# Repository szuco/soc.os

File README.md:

# KiCad SwitchStack

Dreistufiges ESP32-Steuerungsmodul für eine massive Schalter-Unterputzdose (61 mm tief).
Drei gestapelte Leiterplatten steuern zwei 24-V-Jalousiemotoren, lesen Sensorik aus und
kommunizieren primär über RS-485. **Bottom und Mid sind rund (Ø 52 mm) und sitzen in der
Dose; Top ist quadratisch (47 × 47 mm) und sitzt davor** — hinter der Busch-Jaeger
Zentralscheibe 6435-914, deren Drucktasten in den Ecken liegen.

## Zentrale Designregel

Das System ist konsequent in drei Stör- und Leistungsdomänen getrennt:

| Ebene      | Projekt                        | Domäne                                   |
|------------|--------------------------------|------------------------------------------|
| **TOP**    | `hardware/top_ui`              | UI und Sensorik                          |
| **MID**    | `hardware/mid_logic`           | Digitale Logik und Kommunikation         |
| **BOTTOM** | `hardware/bottom_power_motor`  | 24-V-Leistung, Motoren, DC/DC            |

Hochstrom bleibt **vollständig** auf dem Bottom-Board. Die Board-to-Board-Stackverbinder
transportieren ausschließlich Signale und Kleinleistung. Diese Trennung ist für Bauraum,
EMV, Messqualität und Wartbarkeit zentral.

## Eckdaten

- Versorgung: 24 V DC über zwei Adern
- 2 × Klappladenmotor 24 V DC ±10 %, 2 Adern, Umpolung — Laufstrom ≈ 0,3–1,0 A, Blockierstrom offen
- Herrnhuter Mini-Weihnachtsstern 6,0–6,5 V / 0,5 W / ≈ 80 mA, nur im 24-V-Normalbetrieb
- USB-C ausschließlich für Programmierung und Debug
- Positionserkennung ausschließlich über Stromverlauf und Timeout, keine Endschalter
- KiCad-Version: **10.0.5** (migriert von 9.0.7, siehe `docs/08-kicad-workflow.md`)

## Dokumentation

| Dokument | Inhalt |
|---|---|
| [`docs/00-system-overview.md`](docs/00-system-overview.md) | Gesamtsystem, Peripherie, Board-Aufteilung |
| [`docs/01-power-tree.md`](docs/01-power-tree.md) | Power-Tree, Strombilanz, USB-ORing, Schutz |
| [`docs/02-motor-control.md`](docs/02-motor-control.md) | H-Bridges, Strommessung, Überstromschutz, Software-Konzept |
| [`docs/03-stack-pinout.md`](docs/03-stack-pinout.md) | Stackverbinder, verbindliches Pinmapping |
| [`docs/04-mechanical.md`](docs/04-mechanical.md) | Outline, Bohrbild, Koordinaten, Tiefenbudget |
| [`docs/05-manufacturing.md`](docs/05-manufacturing.md) | Lagenaufbau, Kupfer, DRC, Fertigungsdaten |
| [`docs/06-open-decisions.md`](docs/06-open-decisions.md) | Offene Bauteil- und Auslegungsentscheidungen |
| [`docs/07-roadmap.md`](docs/07-roadmap.md) | Konkrete Arbeitsschritte in Reihenfolge |
| [`docs/08-kicad-workflow.md`](docs/08-kicad-workflow.md) | KiCad-Konventionen, Bedienhinweise, Repo-Regeln |
| [`docs/09-display-and-mcu.md`](docs/09-display-and-mcu.md) | Displaywahl, MCU, GPIO-Budget, ESPHome-Grenzen |
| [`docs/10-firmware-strategy.md`](docs/10-firmware-strategy.md) | Firmware-Schichten, ESPHome-Unabhängigkeit, Modbus-Pfad |
| [`docs/11-motor-data.md`](docs/11-motor-data.md) | Motordatenblatt, Leistungsanalyse, **Messprotokoll M1–M7** |
| [`docs/12-legacy-socos.md`](docs/12-legacy-socos.md) | Vorgängerprojekt SoC OS: übernommene Anforderungen, verlorene Funktionen, Restriktionen |
| [`docs/13-funktionsstatus.md`](docs/13-funktionsstatus.md) | **Was steht, was fehlt** — Hardware, Firmware und Mechanik nebeneinander |
| [`hardware/bom/README.md`](hardware/bom/README.md) | Beschaffungsliste, Fertigerempfehlung, Bestellweg |

## Repository-Struktur

```
hardware/
  bottom_power_motor/   KiCad BOTTOM (24 V, Motor, DC/DC)
  mid_logic/            KiCad MID (ESP32-S3, RS-485, Expander, PhotoMOS, Piezo)
  top_ui/               KiCad TOP (USB-C, Display 1,69", 4 Ecktaster, SHT4x, ToF, Stern)
  lib/                  Gemeinsame Symbol-/Footprint-/3D-Bibliotheken
  bom/                  Beschaffung und Fertigerempfehlung
  fab/                  Erzeugte Fertigungsdaten und der Nutzen (Build-Ergebnis)
mechanical/             Adapter zur BJ-Zentralscheibe: build123d-Modell, STEP/STL
tools/                  Generatoren (Mechanik, Schaltpläne, Layouts, Routing, Fertigung)
firmware/
  esphome/              ESPHome-Konfiguration für Home Assistant
docs/                   Projektübergreifende Spezifikationen
```

Ein Verzeichnis `archive/` mit dem Altbestand der Vorgängerprojekte gab es bis zum
15.08.2026. Es ist ausgewertet und entfernt; das Ergebnis steht in
[`docs/12-legacy-socos.md`](docs/12-legacy-socos.md), die Dateien selbst liegen nur
noch in der Git-Historie.

## Erzeugen

Die mechanischen Teile sind **generiert, nicht handgezeichnet** — damit können die drei
Boards nicht auseinanderlaufen:

```bash
python3 tools/gen_boards.py          # 3 × .kicad_pcb: Outline, Bohrbild, Keepout
python3 tools/gen_bottom_sch.py      # Bottom-Schaltplan + BOM, mit Netzlistenprüfung
python3 tools/gen_mid_sch.py         # Mid-Schaltplan (ESP32, RS-485, Expander)
python3 tools/gen_top_sch.py         # Top-Schaltplan (USB-C, Taster, Sensorik)
python3 tools/gen_layouts.py         # 3 Layouts: Platzierung, Netze, Zonen, DRC
python3 tools/route_boards.py        # Freerouting-Pipeline (Container, s. docs/05)
python3 tools/gen_fab.py [board]     # Gerber/Drill/Pos + BOMs, nur nach DRC-Gate
python3 tools/gen_panel.py           # Fertigungsnutzen aus den drei Quellprojekten
python3 mechanical/adapter.py        # Adapter für die BJ-Zentralscheibe, mit Selbsttest
```

Jedes dieser Skripte prüft sein Ergebnis und meldet Abweichungen. `gen_boards.py`,
`gen_layouts.py`, `gen_fab.py` und `gen_panel.py` brauchen die `pcbnew`-Python-API aus
einer KiCad-Installation, `adapter.py` braucht `build123d` (`pip install build123d`),
`route_boards.py` einen Container (siehe `docs/05`).

Dazu zwei Werkzeuge ohne Hardware: `python3 tools/display_mock.py` zeichnet den
Displayinhalt als PNG, und `esphome compile firmware/esphome/switchstack.yaml`
übersetzt die Firmware vollständig.

Auch der Bottom-Schaltplan wird erzeugt: Die Konnektivität steht als Quelltext, und
nach dem Schreiben liest `kicad-cli` die Netzliste zurück und vergleicht sie gegen
genau diese Vorgabe. Das Ergebnis ist zweckmäßig gezeichnet, aber nachweislich
korrekt — und in KiCad frei umarrangierbar.

## Status

Vollständige Gegenüberstellung von umgesetzten und fehlenden Funktionen:
[`docs/13-funktionsstatus.md`](docs/13-funktionsstatus.md).

| Teil | Stand |
|---|---|
| Systemspezifikation, Power-Tree, Pinmapping | dokumentiert |
| Mechanik der drei Boards | erzeugt und verifiziert |
| Front | **Serienteil**: BJ-Zentralscheibe 6435-914 im Rahmen 1721-914. Der **Adapter** dazwischen ist erzeugt und selbstgeprüft (`mechanical/adapter.py`) |
| Schaltpläne aller drei Boards + Stücklisten | **erzeugt und netzlistengeprüft** — Schaltungsreview gegen Datenblätter steht aus |
| Layouts aller drei Boards: Platzierung + Zonen | **erzeugt, DRC ohne Platzierungsfehler** |
| **Routing BOTTOM** | 985 Segmente, 102 Vias, **43 Verbindungen offen** — Rest Handarbeit (docs/05 verlangt das für Leistungspfade ohnehin) |
| **Routing MID** | **746 Segmente, 104 Vias** (16.08.2026, Container). Offen: 18 Signalverbindungen und **ein Kurzschluss** `HOOD_B`/`RELAY_LED` an einer Stelle — Handarbeit, s. docs/05 |
| **Routing TOP** | **197 Segmente, 12 Vias** (16.08.2026, Container). Offen: 14 Signale, darunter **alle vier Tastenleitungen und drei USB-Netze**; dazu **eine neue Kollision** einer Leiterbahn mit dem Befestigungsloch der USB-Buchse |
| Fertigungsnutzen (3 Platinen in einer Boarddatei) | **erzeugt:** `hardware/fab/panel/` — 173,4 × 64,4 mm, zwei Kreise + ein Quadrat |
| Fertigungsdaten | **keine** — `python3 tools/gen_fab.py` nach dem Routing, mit DRC-Gate |
| ESPHome-Firmware | **übersetzt** (`esphome compile`, 2026.7.4 / IDF 5.5.5): RAM 35 %, Flash 56 %. Alle Lambdas geprüft. Motoren fahren **auf Zeit** |
| Lasterkennung, ToF-Distanz, RS-485-Protokoll | **fehlen** — die ersten beiden brauchen eine eigene C++-Komponente, s. docs/13 |
| Gefertigt oder gemessen | **nichts** |

Nächste Schritte: [`docs/07-roadmap.md`](docs/07-roadmap.md).
Der kritische Pfad ist die Messung des Blockierstroms — Messprotokoll in
[`docs/11-motor-data.md`](docs/11-motor-data.md), Abschnitt 4. Ohne sie bleiben
Sicherungen, Trip-Schwellen, Treiberauswahl und Steckverbinder provisorisch.

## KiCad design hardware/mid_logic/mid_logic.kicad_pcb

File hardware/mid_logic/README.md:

# MID – Logic

KiCad-Projekt `mid_logic`. Logik- und Kommunikationsebene des Stacks.

## Umfang

Bestückt sind 37 Bauteile, 57 Netze (`bom_mid.csv`):

- **ESP32-S3-WROOM-1-N16R8** als zentrale Steuerung, RESET- und BOOT-Taster
- **MAX3485** als **primäre** Kommunikation: `RS485_DIR` schaltet DE und /RE
  gemeinsam, Fail-Safe-Bias 2 × 560 R, Terminierung 120 R als **DNP** (nur am
  Busende bestücken), JST-XH 3-polig
- **PCF8574** (0x20) als GPIO-Expander für die langsamen Signale: `HW_TRIP1/2`,
  `TRIP_RST`, `STAR_EN`, `PRESENCE_INT`, `RELAY_CTL`, `REED1/2` — **P0–P7 sind
  damit restlos belegt** (relevant für Punkt 34)
- **Piezo passiv** mit Treiberstufe — ein aktiver Summer kann keine Melodien
- **PhotoMOS AQY282GS** als potentialfreier Meldekontakt zur Dunstabzugshaube,
  **ausschließlich SELV**, mit 33-V-Klemmdiode
- **Feldstecker JST-SH 6-polig** für zwei Verschlusskontakte und die Haube,
  je Reed 10k Pull-up, 1k Serie und 5V6-ESD-Diode
- Stackverbinder `J_STK_A` und `J_STK_B` nach unten und nach oben

Ein externer ADC ist **nicht** bestückt — die Strommessung hängt am internen ADC
des S3 (offener Punkt 18). Die frühere Radar-Schnittstelle ist entfallen; der
Präsenzsensor sitzt als VL53L1X auf dem Top-Board.

## Kernregeln

- **Antennen-Keepout:** ESP32-Antennenbereich kupfer- und bauteilfrei auf **allen** Lagen,
  Antenne möglichst zur Front orientiert. WLAN ist sekundär — in einer massiven
  Unterputzdose ist die Performance realistisch schwach, deshalb RS-485 als primäre
  Kommunikation.
- Keine Motorströme, keine USB-Datenleitungen auf diesem Board.
- Durchgehende GND-Referenzlage, 4 Lagen empfohlen.

## Mechanik

- Ø 52,0 mm, 1,0 mm Dicke
- Bohrbild und Stackverbinder-Positionen **deckungsgleich** mit BOTTOM und TOP
- Abstand nach unten und nach oben je **10 mm** — gleicher Verbinder, gleicher Abstand

Exakte Koordinaten: [`../../docs/04-mechanical.md`](../../docs/04-mechanical.md)

## Referenzdokumente

- [`docs/03-stack-pinout.md`](../../docs/03-stack-pinout.md) – Pinmapping beider Verbinder
- [`docs/00-system-overview.md`](../../docs/00-system-overview.md) – Peripherieübersicht
- [`docs/06-open-decisions.md`](../../docs/06-open-decisions.md) – ESP32-Modul, Transceiver, ADC, Feldstecker
- [`docs/13-funktionsstatus.md`](../../docs/13-funktionsstatus.md) – Gesamtstand

## Status

**Schaltplan erzeugt und netzlistengeprüft** (`tools/gen_mid_sch.py`, 37 Bauteile,
57 Netze, Netzlistenvergleich bestanden). Stückliste `bom_mid.csv` aus derselben
Quelle.

**Layout:** platziert, Zonen angelegt — **aber ohne eine einzige Leiterbahn.**
Es gab einmal einen vollständig gerouteten Stand (655 Segmente, 73 Vias); der
Umbau auf Reed-Kontakte und Haubenkontakt am 15.08.2026 hat das Layout neu
erzeugt und die Verdrahtung damit verworfen. Sie ist neu zu ziehen — Pipeline:
`tools/route_boards.py`, Massenacharbeit mit `tools/gnd_*.py`.

**Nicht geprüft:** Schaltungsreview gegen Datenblätter (MAX3485-Pinbelegung,
PhotoMOS-LED-Strom). Die Netzliste stimmt mit der Sollvorgabe überein — mehr sagt
sie nicht.

**Offen und layoutrelevant:** Punkt 29 (der Feldstecker sitzt 0,4 mm neben einem
Keepout) und Punkt 34 (Sabotagekontakte hätten hier keinen Expanderpin mehr).

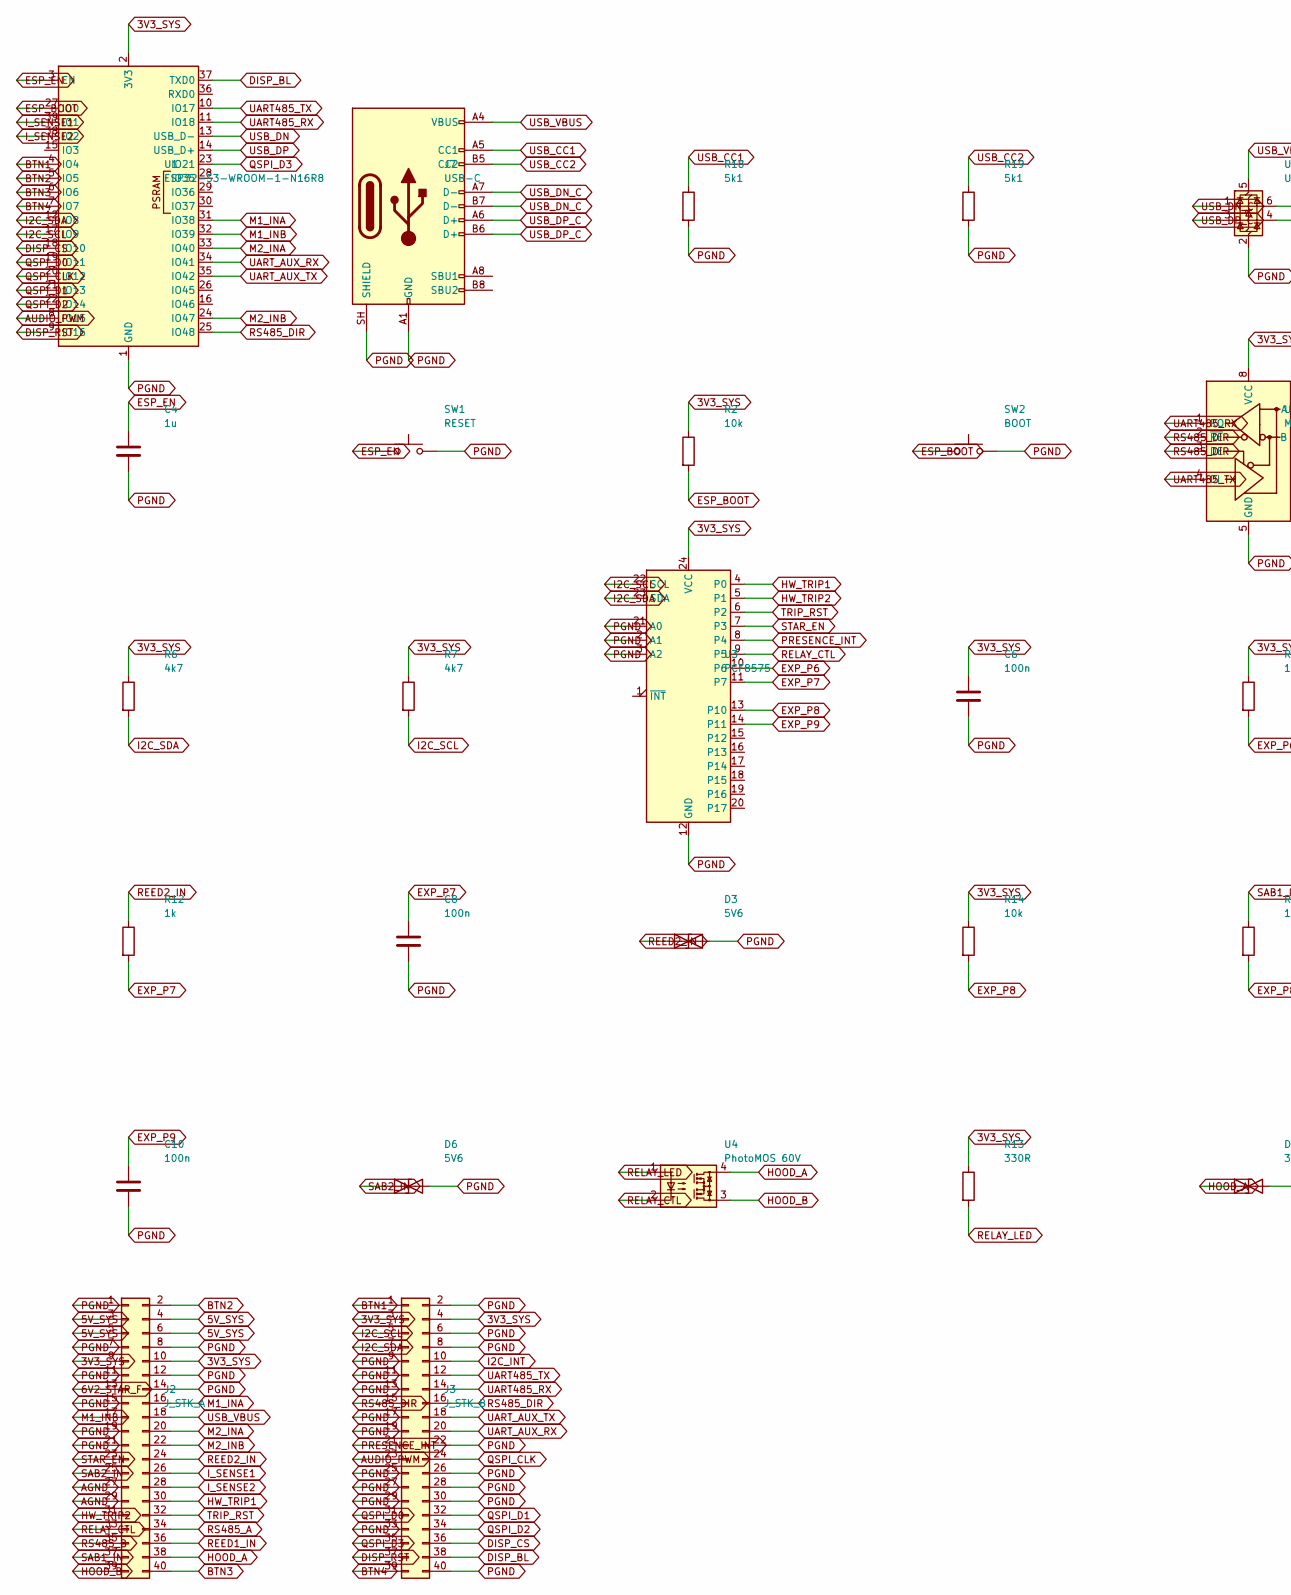
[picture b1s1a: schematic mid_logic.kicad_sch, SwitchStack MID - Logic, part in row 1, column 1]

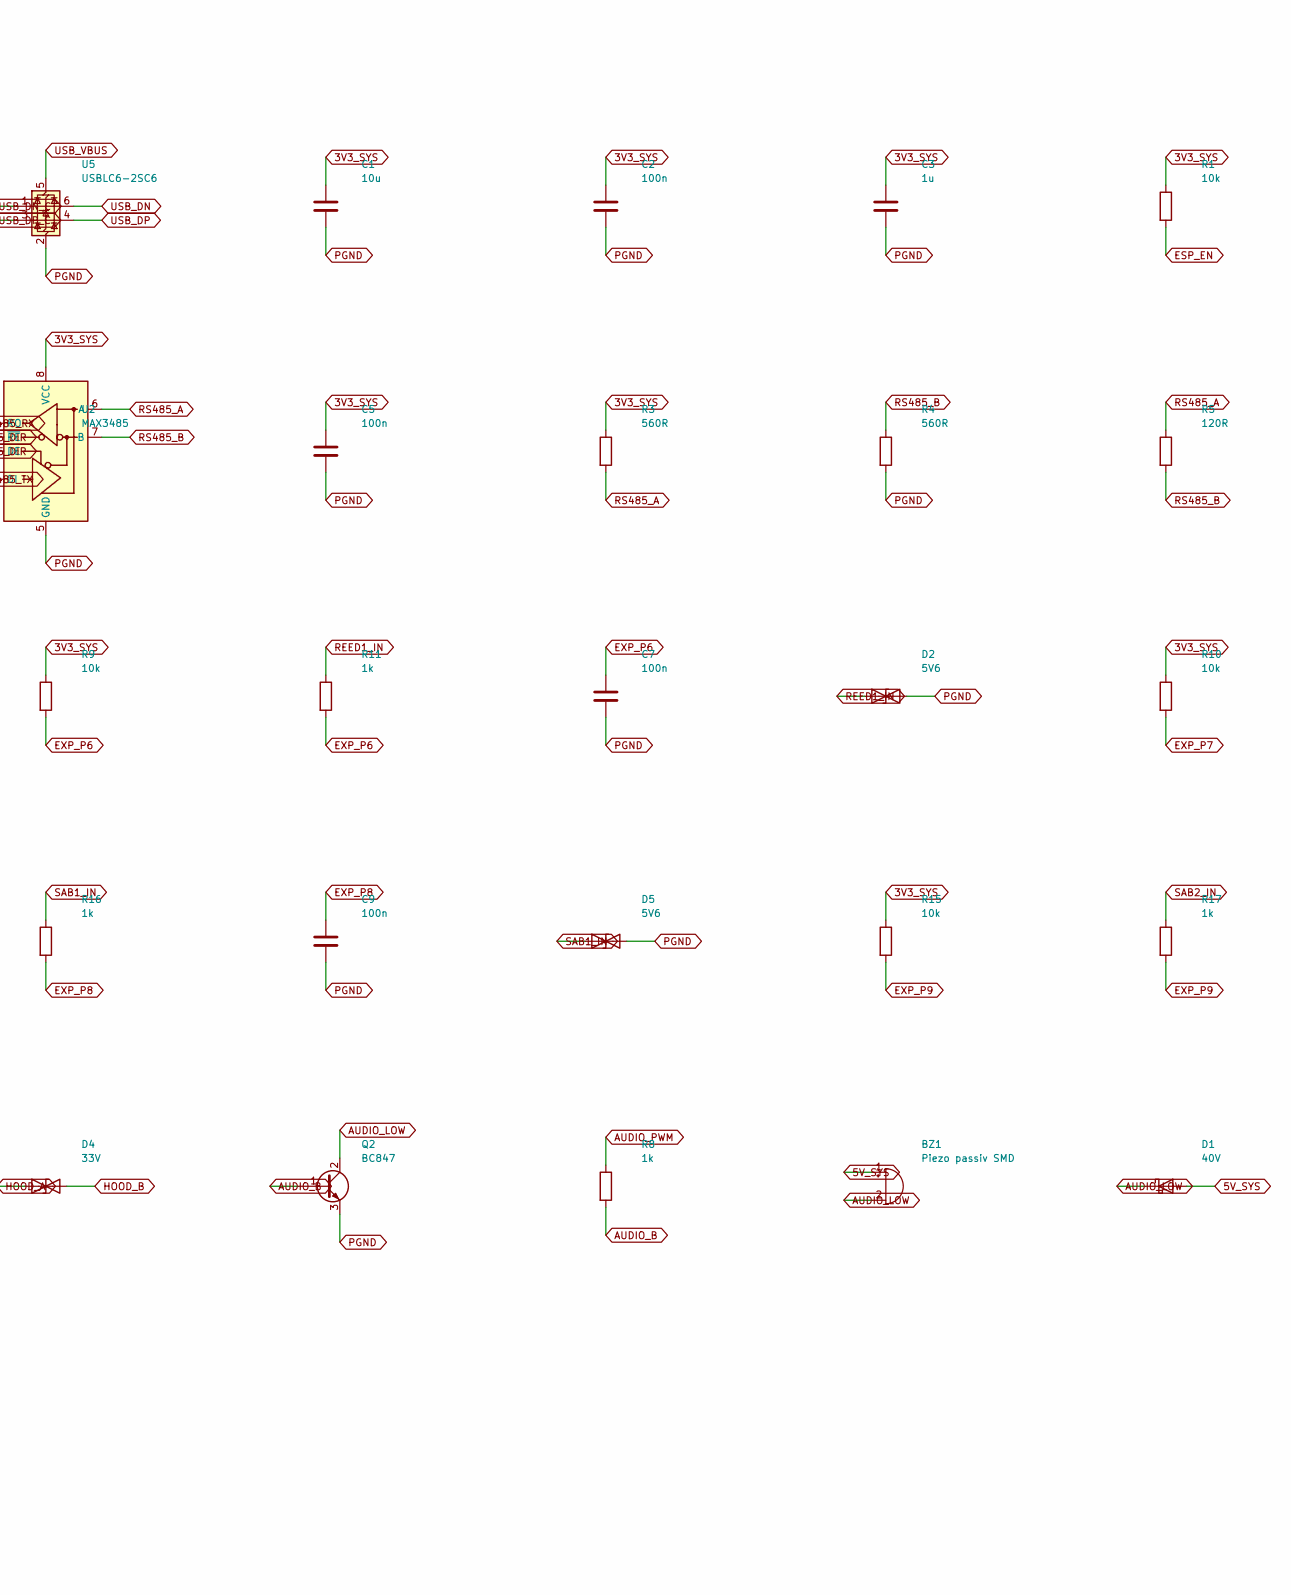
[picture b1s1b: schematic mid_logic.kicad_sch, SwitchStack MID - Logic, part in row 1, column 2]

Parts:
BZ1: Piezo passiv SMD; Buzzer_Murata_PKMCS0909E; MPN Murata PKMCS0909E o.ae., 9 x 9 x 3 mm S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
C1: 10u; C_0805_2012Metric
C2, C5, C6, C7, C8, C9, C10: 100n; C_0603_1608Metric
C3, C4: 1u; C_0603_1608Metric
D1: 40V; D_SOD-123
D2, D3, D5, D6: 5V6; D_SOD-123; MPN ESD am Feldstecker
D4: 33V; D_SOD-123; MPN Klemmung am Haubenausgang
J2: J_STK_A; PinHeader_2x20_P1.27mm_Vertical_Durchsteck
J3: J_STK_B; PinHeader_2x20_P1.27mm_Vertical_Durchsteck
J7: USB-C; USB_C_Receptacle_G-Switch_GT-USB-7051x; MPN G-Switch GT-USB-7051A/B, vertikal SMT (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
Q2: BC847; SOT-23
R1, R2: 10k; R_0603_1608Metric
R3: 560R; R_0603_1608Metric; MPN Fail-Safe-Bias A
R4: 560R; R_0603_1608Metric; MPN Fail-Safe-Bias B
R5: 120R; R_0603_1608Metric; MPN DNP - nur bestuecken, wenn dieses Gerae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
R6, R7: 4k7; R_0603_1608Metric
R8: 1k; R_0603_1608Metric
R9: 10k; R_0603_1608Metric; MPN Pullup Reed 1
R10: 10k; R_0603_1608Metric; MPN Pullup Reed 2
R11: 1k; R_0603_1608Metric; MPN Serie Reed 1
R12: 1k; R_0603_1608Metric; MPN Serie Reed 2
R13: 330R; R_0603_1608Metric; MPN LED-Strom PhotoMOS, ca. 6 mA
R14: 10k; R_0603_1608Metric; MPN Pullup Reed 3
R15: 10k; R_0603_1608Metric; MPN Pullup Reed 4
R16: 1k; R_0603_1608Metric; MPN Serie Reed 3
R17: 1k; R_0603_1608Metric; MPN Serie Reed 4
R18, R19: 5k1; R_0603_1608Metric
SW1: RESET; SW_SPST_TL3342
SW2: BOOT; SW_SPST_TL3342
U1: ESP32-S3-WROOM-1-N16R8; ESP32-S3-WROOM-1; MPN Antenne zeigt zur Front (+Y), Keepout a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
U2: MAX3485; SOIC-8_3.9x4.9mm_P1.27mm; MPN 3,3-V-Typ; Pinbelegung gegen Datenblatt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
U3: PCF8575; SSOP-24_5.3x8.2mm_P0.65mm; MPN Adresse 0x20: A0=A1=A2=GND - muss zur Y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
U4: PhotoMOS 60V; SOP-4_4.4x2.6mm_P1.27mm; MPN 1 Form A, SELV - NICHT fuer Netzspannung
U5: USBLC6-2SC6; SOT-23-6

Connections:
3V3_SYS: C1.1, C2.1, C3.1, C5.1, C6.1, J2.9, J2.10, J3.3, J3.4, R1.1, R2.1, R3.1, R6.1, R7.1, R9.1, R10.1, R13.1, R14.1, R15.1, U1.2 (3V3), U2.8 (VCC), U3.24 (VCC)
5V_SYS: BZ1.1 (+), D1.2 (A), J2.3, J2.4, J2.5, J2.6
6V2_STAR_F: J2.13
AGND: J2.27, J2.29
AUDIO_B: Q2.1 (B), R8.2
AUDIO_LOW: BZ1.2 (-), D1.1 (K), Q2.2 (C)
AUDIO_PWM: J3.23, R8.1, U1.8 (IO15)
BTN1: J3.1, U1.4 (IO4)
BTN2: J2.2, U1.5 (IO5)
BTN3: J2.40, U1.6 (IO6)
BTN4: J3.39, U1.7 (IO7)
DISP_BL: J3.38, U1.37 (TXD0)
DISP_CS: J3.36, U1.18 (IO10)
DISP_RST: J3.37, U1.9 (IO16)
ESP_BOOT: R2.2, SW2.1, U1.27 (IO0)
ESP_EN: C4.1, R1.2, SW1.1, U1.3 (EN)
EXP_P6: C7.1, R9.2, R11.2, U3.10 (P6)
EXP_P7: C8.1, R10.2, R12.2, U3.11 (P7)
EXP_P8: C9.1, R14.2, R16.2, U3.13 (P10)
EXP_P9: C10.1, R15.2, R17.2, U3.14 (P11)
HOOD_A: D4.1 (A1), J2.38, U4.4
HOOD_B: D4.2 (A2), J2.39, U4.3
HW_TRIP1: J2.30, U3.4 (P0)
HW_TRIP2: J2.31, U3.5 (P1)
I2C_INT: J3.10
I2C_SCL: J3.5, R7.2, U1.17 (IO9), U3.22 (SCL)
I2C_SDA: J3.7, R6.2, U1.12 (IO8), U3.23 (SDA)
I_SENSE1: J2.26, U1.39 (IO1)
I_SENSE2: J2.28, U1.38 (IO2)
M1_INA: J2.16, U1.31 (IO38)
M1_INB: J2.17, U1.32 (IO39)
M2_INA: J2.20, U1.33 (IO40)
M2_INB: J2.22, U1.24 (IO47)
PRESENCE_INT: J3.21, U3.8 (P4)
QSPI_CLK: J3.24, U1.20 (IO12)
QSPI_D0: J3.31, U1.19 (IO11)
QSPI_D1: J3.32, U1.21 (IO13)
QSPI_D2: J3.34, U1.22 (IO14)
QSPI_D3: J3.35, U1.23 (IO21)
REED1_IN: D2.1 (A1), J2.36, R11.1
REED2_IN: D3.1 (A1), J2.24, R12.1
RELAY_CTL: J2.33, U3.9 (P5), U4.2
RELAY_LED: R13.2, U4.1
RS485_A: J2.34, R3.2, R5.1, U2.6 (A)
RS485_B: J2.35, R4.1, R5.2, U2.7 (B)
RS485_DIR: J3.15, J3.16, U1.25 (IO48), U2.2 (~RE), U2.3 (DE)
SAB1_IN: D5.1 (A1), J2.37, R16.1
SAB2_IN: D6.1 (A1), J2.25, R17.1
STAR_EN: J2.23, U3.7 (P3)
TRIP_RST: J2.32, U3.6 (P2)
UART485_RX: J3.14, U1.11 (IO18), U2.1 (RO)
UART485_TX: J3.12, U1.10 (IO17), U2.4 (DI)
UART_AUX_RX: J3.20, U1.34 (IO41)
UART_AUX_TX: J3.18, U1.35 (IO42)
USB_CC1: J7.A5 (CC1), R18.1
USB_CC2: J7.B5 (CC2), R19.1
USB_DN: U1.13 (USB_D-), U5.6 (I/O1)
USB_DN_C: J7.A7 (D-), J7.B7 (D-), U5.1 (I/O1)
USB_DP: U1.14 (USB_D+), U5.4 (I/O2)
USB_DP_C: J7.A6 (D+), J7.B6 (D+), U5.3 (I/O2)
USB_VBUS: J2.18, J7.A4 (VBUS), J7.A9 (VBUS), J7.B4 (VBUS), J7.B9 (VBUS), U5.5 (VBUS)

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
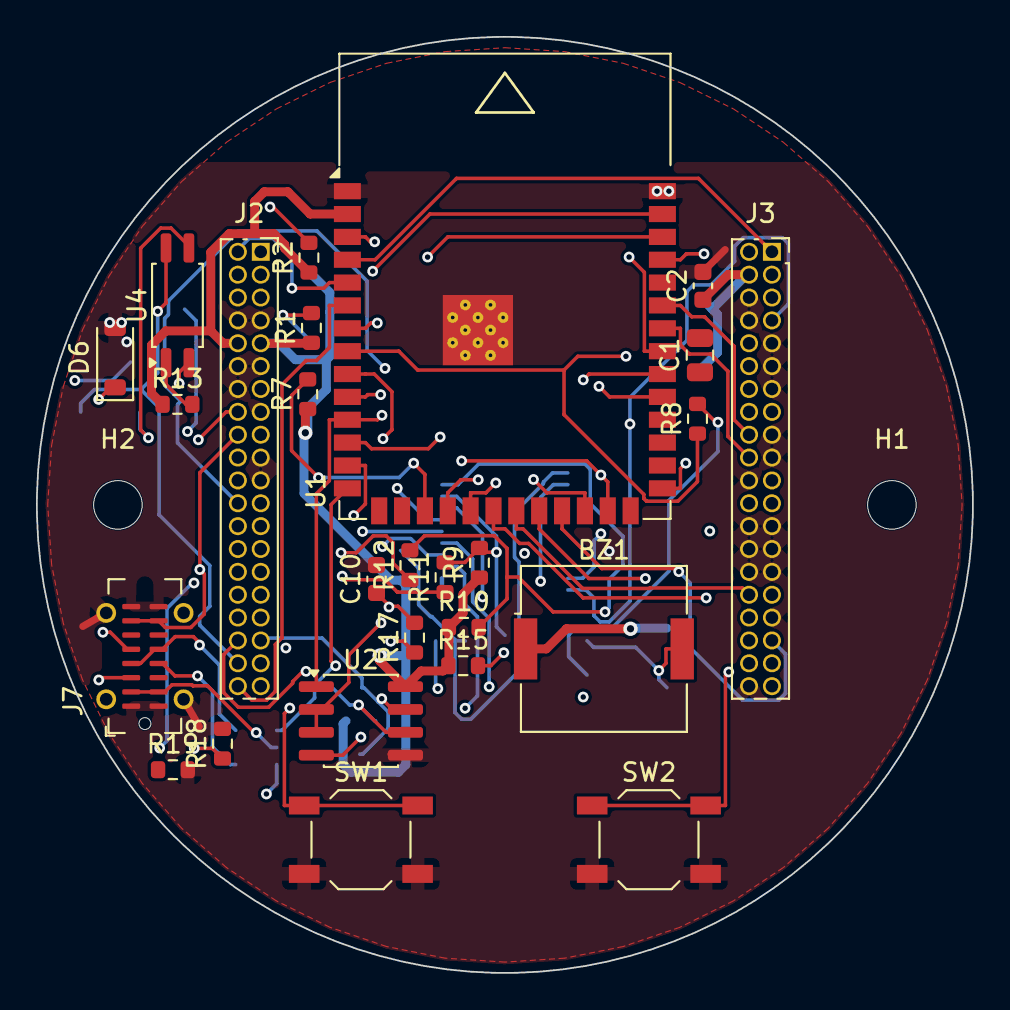
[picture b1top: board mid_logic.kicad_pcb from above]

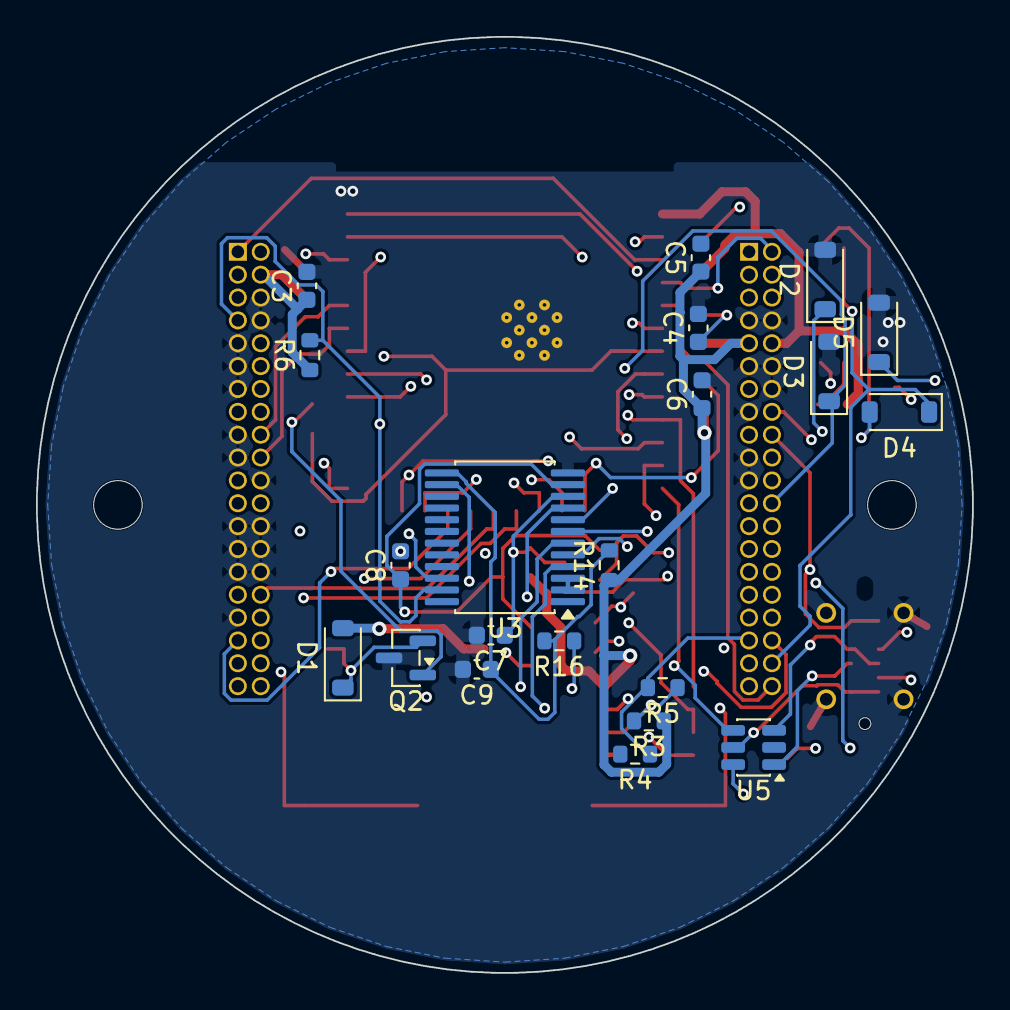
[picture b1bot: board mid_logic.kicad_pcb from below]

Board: 4 copper layers, 52.0 x 52.0 mm, 49 parts (21 on the bottom side), 60 nets.

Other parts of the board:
H1, H2: MountingHole_2.7mm_M2.5

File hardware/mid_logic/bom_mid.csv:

Menge,Designator,Wert,Footprint,Hinweis
1,BZ1,Piezo passiv SMD,Buzzer_Beeper:Buzzer_Murata_PKMCS0909E,"Murata PKMCS0909E o.ae., 9 x 9 x 3 mm SMD - passiv, ein aktiver Summer kann keine rtttl-Melodien. SMD statt des frueheren THT-Typs (12 x 9,5): der blockierte beide Platinenseiten, und auf der Rueckseite fehlte danach der Platz fuer den 16-Bit-Expander"
1,C1,10u,Capacitor_SMD:C_0805_2012Metric,
7,"C2,C5,C6,C7,C8,C9,C10",100n,Capacitor_SMD:C_0603_1608Metric,
2,"C3,C4",1u,Capacitor_SMD:C_0603_1608Metric,
1,D1,40V,Diode_SMD:D_SOD-123,
4,"D2,D3,D5,D6",5V6,Diode_SMD:D_SOD-123,ESD am Feldstecker
1,D4,33V,Diode_SMD:D_SOD-123,Klemmung am Haubenausgang
1,J2,J_STK_A,Connector_PinSocket_1.27mm:PinSocket_2x20_P1.27mm_Vertical,
1,J3,J_STK_B,Connector_PinSocket_1.27mm:PinSocket_2x20_P1.27mm_Vertical,
1,J4,RS485 A/B/GND,Connector_JST:JST_XH_B3B-XH-A_1x03_P2.50mm_Vertical,Kabel VOR dem Stapeln stecken - Zugaenglichkeit im Review pruefen
1,J5,Feld: 4 Reed,Connector_JST:JST_SH_BM06B-SRSS-TB_1x06-1MP_P1.00mm_Vertical,1 REED1 2 SAB1 3 GND | 4 REED2 5 SAB2 6 GND
1,J6,Haubenkontakt,Connector_JST:JST_SH_BM02B-SRSS-TB_1x02-1MP_P1.00mm_Vertical,potentialfrei ueber den PhotoMOS - NUR SELV
1,Q2,BC847,Package_TO_SOT_SMD:SOT-23,
2,"R1,R2",10k,Resistor_SMD:R_0603_1608Metric,
1,R3,560R,Resistor_SMD:R_0603_1608Metric,Fail-Safe-Bias A
1,R4,560R,Resistor_SMD:R_0603_1608Metric,Fail-Safe-Bias B
1,R5,120R,Resistor_SMD:R_0603_1608Metric,"DNP - nur bestuecken, wenn dieses Geraet am Busende sitzt"
2,"R6,R7",4k7,Resistor_SMD:R_0603_1608Metric,
1,R8,1k,Resistor_SMD:R_0603_1608Metric,
1,R9,10k,Resistor_SMD:R_0603_1608Metric,Pullup Reed 1
1,R10,10k,Resistor_SMD:R_0603_1608Metric,Pullup Reed 2
1,R11,1k,Resistor_SMD:R_0603_1608Metric,Serie Reed 1
1,R12,1k,Resistor_SMD:R_0603_1608Metric,Serie Reed 2
1,R13,330R,Resistor_SMD:R_0603_1608Metric,"LED-Strom PhotoMOS, ca. 6 mA"
1,R14,10k,Resistor_SMD:R_0603_1608Metric,Pullup Reed 3
1,R15,10k,Resistor_SMD:R_0603_1608Metric,Pullup Reed 4
1,R16,1k,Resistor_SMD:R_0603_1608Metric,Serie Reed 3
1,R17,1k,Resistor_SMD:R_0603_1608Metric,Serie Reed 4
1,SW1,RESET,Button_Switch_SMD:SW_SPST_TL3342,
1,SW2,BOOT,Button_Switch_SMD:SW_SPST_TL3342,
1,U1,ESP32-S3-WROOM-1-N16R8,RF_Module:ESP32-S3-WROOM-1,"Antenne zeigt zur Front (+Y), Keepout auf allen Lagen"
1,U2,MAX3485,Package_SO:SOIC-8_3.9x4.9mm_P1.27mm,"3,3-V-Typ; Pinbelegung gegen Datenblatt pruefen"
1,U3,PCF8575,Package_SO:SSOP-24_5.3x8.2mm_P0.65mm,Adresse 0x20: A0=A1=A2=GND - muss zur YAML passen
1,U4,PhotoMOS 60V,Package_SO:SOP-4_4.4x2.6mm_P1.27mm,"1 Form A, SELV - NICHT fuer Netzspannung"

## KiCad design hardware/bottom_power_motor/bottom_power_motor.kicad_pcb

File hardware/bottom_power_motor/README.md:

# BOTTOM – Power & Motor

KiCad-Projekt `bottom_power_motor`. Leistungsebene des Stacks.

## Umfang

- 24-V-Eingangsschutz: Sicherung, TVS, optionaler Verpolschutz
- Hochstrom-Steckverbinder nach unten, 6-polig
- Zwei Motor-H-Bridges für die Jalousiemotoren
- Strommessung getrennt pro Motor
- Hardwareseitige Überstromabschaltung, Comparator + Latch **pro Motor**
- DC/DC-Wandler: 24 → 5 V, 5 → 3,3 V, 24 → 6,2 V
- Mini-Relais (Zuordnung noch zu bestätigen)
- Stackverbinder `J_STK_A` und `J_STK_B` nach oben

## Kernregel

**Hochstrom bleibt vollständig auf diesem Board.** Motorströme werden niemals über die
Stackverbinder geführt.

## Mechanik

- Ø 52,0 mm, 1,0 mm Dicke
- Zwei Befestigungsbohrungen auf R = 21,5 mm bei 0° / 180° (Bohrbild v2, siehe docs/04)
- Bottom-Connector im Bereich −Y (unten), siehe Frontorientierung
- 2-oz-Kupfer prüfen

Exakte Koordinaten: [`../../docs/04-mechanical.md`](../../docs/04-mechanical.md)

## Referenzdokumente

- [`docs/01-power-tree.md`](../../docs/01-power-tree.md) – Power-Tree, Strombilanz, Schutz
- [`docs/02-motor-control.md`](../../docs/02-motor-control.md) – H-Bridges, Sense, Trip
- [`docs/03-stack-pinout.md`](../../docs/03-stack-pinout.md) – Stackverbinder
- [`docs/04-mechanical.md`](../../docs/04-mechanical.md) – Outline, Bohrbild, Tiefenbudget

## Dateien

| Datei | Stand |
|---|---|
| `bottom_power_motor.kicad_pcb` | Mechanik: Outline Ø 52 mm, Bohrbild, Dicke 1,0 mm |
| `bottom_power_motor.kicad_sch` | **Schaltplan, 103 Bauteile, 105 Netze** |
| `bom_bottom.csv` | Stückliste, aus derselben Quelle erzeugt |

Beides wird generiert, nicht von Hand gezeichnet:

```bash
python3 tools/gen_boards.py       # Mechanik
python3 tools/gen_bottom_sch.py   # Schaltplan + Stückliste + Netzlistenprüfung
```

## Status

**Schaltplan steht und ist netzlistengeprüft.** `tools/gen_bottom_sch.py` exportiert
nach dem Erzeugen die Netzliste mit `kicad-cli` und vergleicht sie gegen die im
Quelltext hinterlegte Soll-Konnektivität — 105 Netze, keine Abweichung, kein offener
Pin.

Enthalten: 24-V-Eingangsschutz (Sicherung, TVS, P-FET-Verpolschutz), 12-V-Gate-
Versorgung, drei DC/DC-Wandler, USB-ORing, Stern-Ausgang mit Polyfuse, zwei
vollständige H-Brücken aus je 2× IR2104 und 4 N-FETs, Inline-Strommessung mit
INA240A2, Fensterkomparator und Latch je Kanal, beide Stackverbinder.

**Was der Schaltplan noch nicht ist:**

- **Nicht geprüft im Sinne einer Schaltungsreview.** Werte sind gerechnet, aber die
  Regler sind noch nicht gegen die Hersteller-Referenzlayouts abgeglichen.
- **Pinbelegungen der ICs gegen die Datenblätter prüfen** — insbesondere INA240A2D,
  dessen KiCad-Symbol zwei GND-Pins gestapelt führt.
- **Die Darstellung ist zweckmäßig, nicht schön.** Jedes Bauteil hängt über kurze
  Stummel an globalen Labels. Das ist netzlistenidentisch mit einem gezeichneten Plan
  und lässt sich in KiCad frei umarrangieren, ohne die Verbindungen zu verlieren.

**Layout:** Platzierung generiert, Zonen gefüllt, **985 Segmente und 102 Vias**
geroutet, keine Kupferfehler. Offen sind **43 Verbindungen im Motor- und
Leistungsteil** (SW-Knoten, Gate-Netze, `24V_PROT`). Der Autorouter konvergiert
dort nicht mehr — und soll es auch nicht: Diese Pfade sind laut
[`docs/05`](../../docs/05-manufacturing.md) Abschnitt 3 **von Hand** zu ziehen,
kurz und breit, Buck-Schleifen nach Hersteller-Referenzlayout, Sternpunkt
AGND/PGND über R12. Erst danach greift das DRC-Gate von `gen_fab.py`.

Offene Bauteilposition: der N-Kanal-MOSFET (Punkt 8 in
[`docs/06`](../../docs/06-open-decisions.md)) — er hängt am noch nicht gemessenen
Blockierstrom.

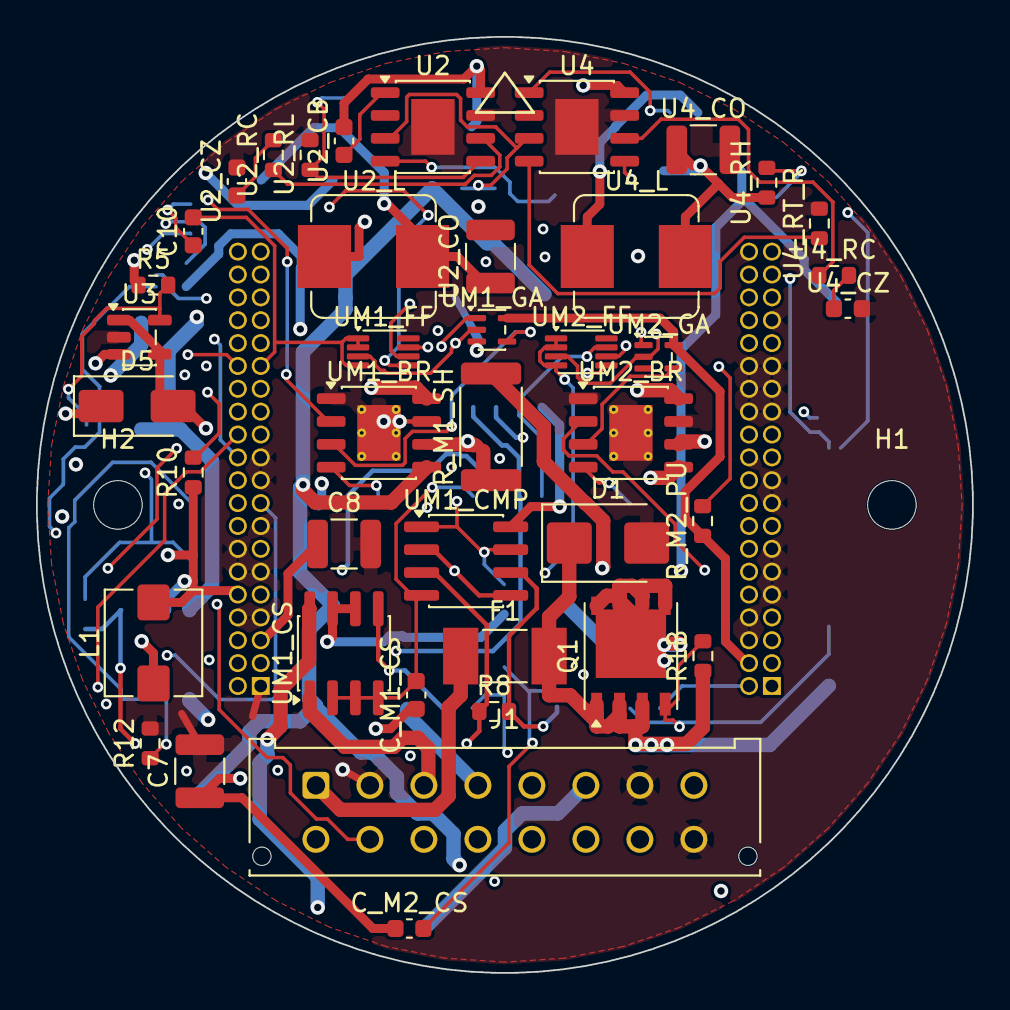
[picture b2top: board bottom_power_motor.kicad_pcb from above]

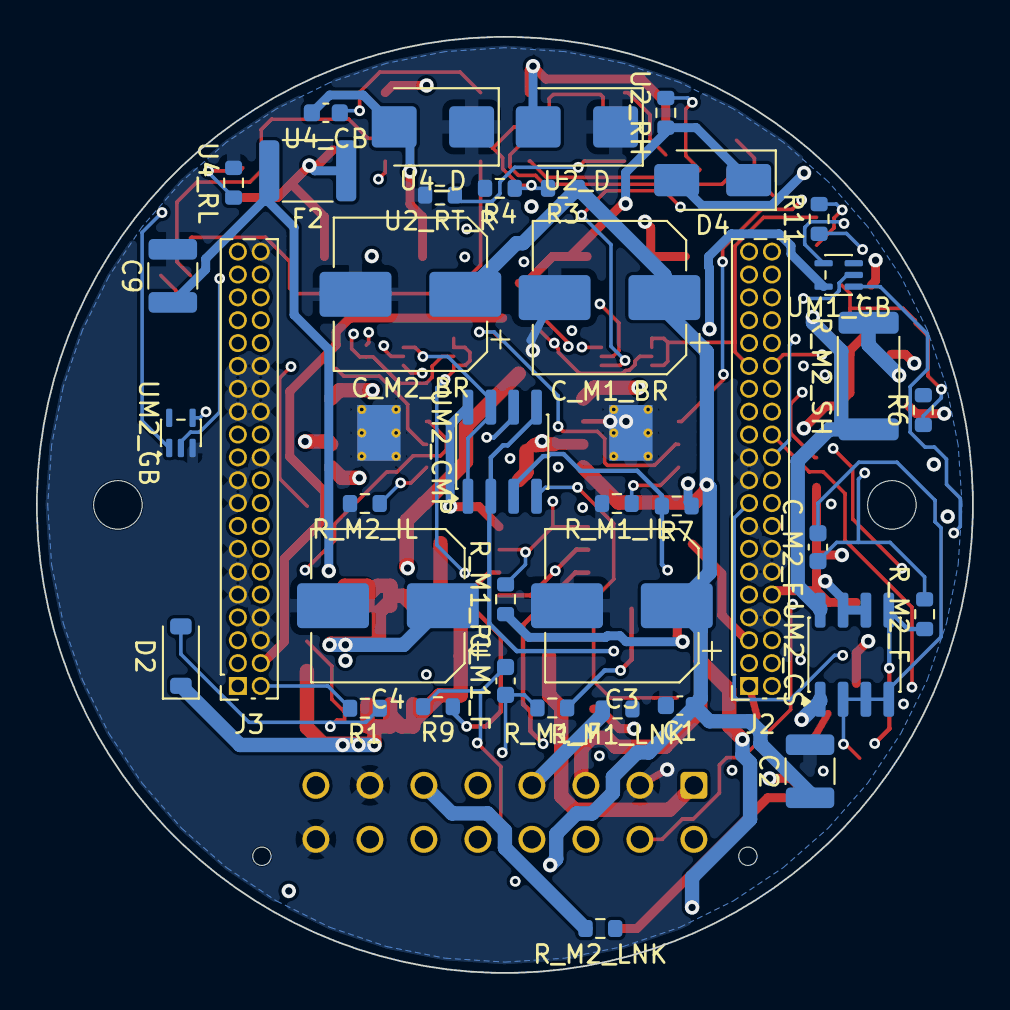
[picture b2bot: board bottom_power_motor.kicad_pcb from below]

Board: 4 copper layers, 52.0 x 52.0 mm, 82 parts (39 on the bottom side), 67 nets.

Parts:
C1, C10: 100n; C_0603_1608Metric
C2: 10u; C_1210_3225Metric
C3, C4: 220u/35V Polymer; CP_Elec_8x6.5
C7, C8, C9: 22u; C_1210_3225Metric
C_M1_BR, C_M2_BR: 100u/35V Polymer; CP_Elec_8x6.5
C_M1_CS, C_M2_CS: 100n; C_0603_1608Metric
C_M1_F, C_M2_F: 1n; C_0603_1608Metric
D1: SMBJ30A; D_SMB
D2: 12V; D_SOD-123
D4, D5: 40V 3A; D_SMA
F1: 15A flink; Fuse_Littelfuse-NANO2-451_453
F2: 0.5A; Fuse_1812_4532Metric
H1, H2: MountingHole_2.7mm_M2.5
J1: Feld 16p; Molex_Micro-Fit_3.0_43045-1612_2x08_P3.00mm_Vertical
J2: J_STK_A; PinSocket_2x20_P1.27mm_Vertical
J3: J_STK_B; PinSocket_2x20_P1.27mm_Vertical
L1: 2u2; L_Bourns_SRP5030T
Q1: P-FET 40V 30A; PowerPAK_SO-8_Single
R1, R10: 100k; R_0603_1608Metric
R1B: 1M; R_0603_1608Metric
R3: 392k; R_0603_1608Metric
R4: 88k7; R_0603_1608Metric
R5: 180k; R_0603_1608Metric
R6, R8: 40k2; R_0603_1608Metric
R7, R9: 10k0; R_0603_1608Metric
R11: 1k; R_0603_1608Metric
R12: 0R; R_0603_1608Metric
R_M1_F, R_M2_F: 1k; R_0603_1608Metric
R_M1_IL, R_M2_IL: 33k0; R_0603_1608Metric
R_M1_LNK, R_M2_LNK: 0R; R_0603_1608Metric
R_M1_PU, R_M2_PU: 10k; R_0603_1608Metric
R_M1_SH, R_M2_SH: 5m0 1W; R_2512_6332Metric
U2, U4: TPS54360; HSOP-8-1EP_3.9x4.9mm_P1.27mm_EP2.41x3.1mm
U2_CB, U4_CB: 100n; C_0603_1608Metric
U2_CO: 47u; C_1210_3225Metric
U2_CZ, U4_CZ: 3n3; C_0603_1608Metric
U2_D, U4_D: 60V 3A; D_SMB
U2_L: 10u; L_Bourns_SRP7028A_7.3x6.6mm
U2_RC, U4_RC: 10k; R_0603_1608Metric
U2_RH: 53k6; R_0603_1608Metric
U2_RL: 10k2; R_0603_1608Metric
U2_RT_R, U4_RT_R: 100k; R_0603_1608Metric
U3: TLV62569; SOT-23-5
U4_CO: 22u; C_1210_3225Metric
U4_L: 33u; L_Bourns_SRP7028A_7.3x6.6mm
U4_RH: 68k1; R_0603_1608Metric
U4_RL: 10k0; R_0603_1608Metric
UM1_BR, UM2_BR: DRV8871; HSOP-8-1EP_3.9x4.9mm_P1.27mm_EP2.41x3.1mm_ThermalVias
UM1_CMP, UM2_CMP: TLV3702; SOIC-8_3.9x4.9mm_P1.27mm
UM1_CS, UM2_CS: INA240A2; SOIC-8_3.9x4.9mm_P1.27mm
UM1_FF, UM2_FF: 74AUP1G74; VSSOP-8_2.3x2mm_P0.5mm
UM1_GA, UM1_GB, UM2_GA, UM2_GB: 74AHC1G08; SOT-353_SC-70-5

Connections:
3V3_SYS: C7.1, C_M1_CS.1, C_M2_CS.1, J2.9, J2.10, J3.3, J3.4, L1.2, R5.1, R7.1, R10.1, R_M1_PU.1, R_M2_PU.1, UM1_CMP.8, UM1_CS.6, UM1_CS.7, UM1_FF.8, UM1_GA.5, UM1_GB.5, UM2_CMP.8, UM2_CS.6, UM2_CS.7, UM2_FF.8, UM2_GA.5, UM2_GB.5
5V_BUCK: D4.1, U2_CO.1, U2_L.2, U2_RH.1
5V_SYS: C8.1, D4.2, D5.2, J2.3, J2.4, J2.5, J2.6, U3.1, U3.4
6V2_STAR: F2.1, U4_CO.1, U4_L.2, U4_RH.1
6V2_STAR_F: C9.1, F2.2, J2.13
24V_EN: R3.2, R4.1, U2.3, U4.3
24V_F: D1.1, D2.1, F1.2, Q1.1, Q1.2, Q1.3, R1B.1
24V_GATE_P: D2.2, Q1.4, R1.1, R1B.2
24V_IN: F1.1, J1.1
24V_PROT: C1.1, C2.1, C3.1, C4.1, C_M1_BR.1, C_M2_BR.1, Q1.5, R3.1, U2.2, U4.2, UM1_BR.5, UM2_BR.5
AGND: C10.2, C_M1_CS.2, C_M1_F.2, C_M2_CS.2, C_M2_F.2, J2.27, J2.29, R9.2, R12.1, UM1_CMP.4, UM1_CS.2, UM1_CS.3, UM1_CS.4, UM1_FF.1, UM1_FF.2, UM1_FF.4, UM2_CMP.4, UM2_CS.2, UM2_CS.3, UM2_CS.4, UM2_FF.1, UM2_FF.2, UM2_FF.4
EN_LOOP: J3.2, R1.2
HOOD_A: J1.14, J2.38
HOOD_B: J1.15, J2.39
HW_TRIP1: J2.30, UM1_FF.5
HW_TRIP2: J2.31, UM2_FF.5
I_SENSE1: C_M1_F.1, J2.26, R_M1_F.2
I_SENSE2: C_M2_F.1, J2.28, R_M2_F.2
M1_A: J1.3, R_M1_SH.2, UM1_CS.1
M1_B: J1.4, R_M1_LNK.2, UM1_BR.8
M1_GA: UM1_BR.3, UM1_GA.4
M1_GB: UM1_BR.2, UM1_GB.4
M1_ILIM: R_M1_IL.1, UM1_BR.4
M1_INA: J2.16, UM1_GA.1
M1_INB: J2.17, UM1_GB.1
M1_ISNS: R_M1_F.1, UM1_CMP.2, UM1_CMP.5, UM1_CS.5
M1_SD: UM1_FF.3, UM1_GA.2, UM1_GB.2
M1_SWA: R_M1_SH.1, UM1_BR.6, UM1_CS.8
M1_TRIP: R_M1_PU.2, UM1_CMP.1, UM1_CMP.7, UM1_FF.7
M2_A: J1.5, R_M2_SH.2, UM2_CS.1
M2_B: J1.6, R_M2_LNK.2, UM2_BR.8
M2_GA: UM2_BR.3, UM2_GA.4
M2_GB: UM2_BR.2, UM2_GB.4
M2_ILIM: R_M2_IL.1, UM2_BR.4
M2_INA: J2.20, UM2_GA.1
M2_INB: J2.22, UM2_GB.1
M2_ISNS: R_M2_F.1, UM2_CMP.2, UM2_CMP.5, UM2_CS.5
M2_SD: UM2_FF.3, UM2_GA.2, UM2_GB.2
M2_SWA: R_M2_SH.1, UM2_BR.6, UM2_CS.8
M2_TRIP: R_M2_PU.2, UM2_CMP.1, UM2_CMP.7, UM2_FF.7
PGND: C1.2, C2.2, C3.2, C4.2, C7.2, C8.2, C9.2, C_M1_BR.2, C_M2_BR.2, D1.2, J1.2, J1.7, J1.16, J2.1, J2.7, J2.8, J2.11, J2.12, J2.14, J2.15, J2.19, J2.21, J3.6, J3.8, J3.9, J3.11, J3.13, J3.17, J3.19, J3.22, J3.25, J3.26, J3.27, J3.28, J3.29, J3.30, J3.33, J3.40, R4.2, R6.2, R12.2, R_M1_IL.2, R_M2_IL.2, U2.7, U2.9, U2_CO.2, U2_CZ.2, U2_D.1, U2_RL.2, U2_RT_R.2, U3.2, U4.7, U4.9, U4_CO.2, U4_CZ.2, U4_D.1, U4_RL.2, U4_RT_R.2, UM1_BR.1, UM1_BR.7, UM1_BR.9, UM1_GA.3, UM1_GB.3, UM2_BR.1, UM2_BR.7, UM2_BR.9, UM2_GA.3, UM2_GB.3
REED1_IN: J1.10, J2.36
REED2_IN: J1.12, J2.24
RS485_A: J1.8, J2.34
RS485_B: J1.9, J2.35
RS485_DIR: J3.15, J3.16
SAB1_IN: J1.11, J2.37
SAB2_IN: J1.13, J2.25
TRIP_CLR: C10.1, R10.2, R11.2, UM1_FF.6, UM2_FF.6
TRIP_RST: J2.32, R11.1
U2_BOOT: U2.1, U2_CB.1
U2_COMP: U2.6, U2_RC.1
U2_CZ_N: U2_CZ.1, U2_RC.2
U2_FB: U2.5, U2_RH.2, U2_RL.1
U2_RT: U2.4, U2_RT_R.1
U2_SW: U2.8, U2_CB.2, U2_D.2, U2_L.1
U3_FB: R5.2, R6.1, U3.5
U3_SW: L1.1, U3.3
U4_BOOT: U4.1, U4_CB.1
U4_COMP: U4.6, U4_RC.1
U4_CZ_N: U4_CZ.1, U4_RC.2
U4_FB: U4.5, U4_RH.2, U4_RL.1
U4_RT: U4.4, U4_RT_R.1
U4_SW: U4.8, U4_CB.2, U4_D.2, U4_L.1
USB_VBUS: D5.1, J2.18
V_TRIP_HI: R7.2, R8.1, UM1_CMP.3, UM2_CMP.3
V_TRIP_LO: R8.2, R9.1, UM1_CMP.6, UM2_CMP.6
